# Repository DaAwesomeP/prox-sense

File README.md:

prox-sense
==========

[prox-sense](https://github.com/DaAwesomeP/prox-sense) is a series of printed
circuit board (PCB) designs for designed to bring robust and discreet
capacitive proximity and touch sensing to artists and makers.

**Video demonstration and poster: [Hidden Touch: Open Source Sensors for New
Interaction](https://perrynaseck.com/work/prox-sense/)**

This repository contains the KiCAD schematics, boards, and Gerber files
required to produce the sensing boards. License notice below.

## Premise

**Existing systems for creating interactive experiences:**

 - Expensive
 - Can be difficult to use or understand
 - Limited or nonexistent proximity detection (existing capacitive options)
 - Dense arrangements of proximity sensors may not function (existing
   capacitive options)
 - Connectivity options do not scale up to large systems of sensors
 - Equivalent/alternative optical systems are intrusive, expensive, or
   predictable (cameras, vision systems)
 - Require large amounts of processing or setup
 - Existing tactile systems are predictable (buttons, knobs, touchscreens,
   etc.)

**prox-sense promotes discoverable and new interactions:**

 - Inexpensive
 - Focus on proximity detection
 - Proximity through solid and opaque objects (sensors can be entirely hidden)
 - Directional proximity detection options allow for dense arrangements
 - Interaction is led by the objects the sensors are hidden in and the
   resulting interactions, not the sensors and sensor limitations
 - Small sensors allow for small detection areas and objects
 - Simple connectivity scales up to large systems without limiting the maximum
   number of easily-connected sensors
 - Open source and free to produce

## Boards

Currently all boards are based around the [Microchip
MTCH105](https://www.microchip.com/en-us/product/MTCH105)

 - Simple GPIO interface for detection and sensitivity adjustment. The standard
   logic output can be used directly with microcontrollers, logic circuits,
   transistors, muxes, and port expanders
 - Rejects liquids and other uncertain signal sources
 - Supports guard reference signal for solid interference mitigation
 - All boards currently use the same schematic but vary the copper/trace layout
   to achieve different detection patterns

### Directional board

 - Detects proximity and touch only directly in front of the sensors
 - Rejects rear and off-axis (side) detection using guard signal
 - Guard signal on edge allows for close-packing of sensors

### Omnidirectional board

 - Detects proximity and touch from all directions
 - Guard signal on edge allows for close-packing of sensors

## License Notice
Copyright Perry Naseck 2022.

This source describes Open Hardware and is licensed under the CERN-OHL-S v2.

You may redistribute and modify this source and make products using it under
the terms of the CERN-OHL-S v2 (https://ohwr.org/cern_ohl_s_v2.txt).

This source is distributed WITHOUT ANY EXPRESS OR IMPLIED WARRANTY,
INCLUDING OF MERCHANTABILITY, SATISFACTORY QUALITY AND FITNESS FOR A
PARTICULAR PURPOSE. Please see the CERN-OHL-S v2 for applicable conditions.

Source location: https://github.com/DaAwesomeP/prox-sense

As per CERN-OHL-S v2 section 4, should You produce hardware based on this
source, You must where practicable maintain the Source Location visible
on the external case of the prox-sense or other products you make using this
source.

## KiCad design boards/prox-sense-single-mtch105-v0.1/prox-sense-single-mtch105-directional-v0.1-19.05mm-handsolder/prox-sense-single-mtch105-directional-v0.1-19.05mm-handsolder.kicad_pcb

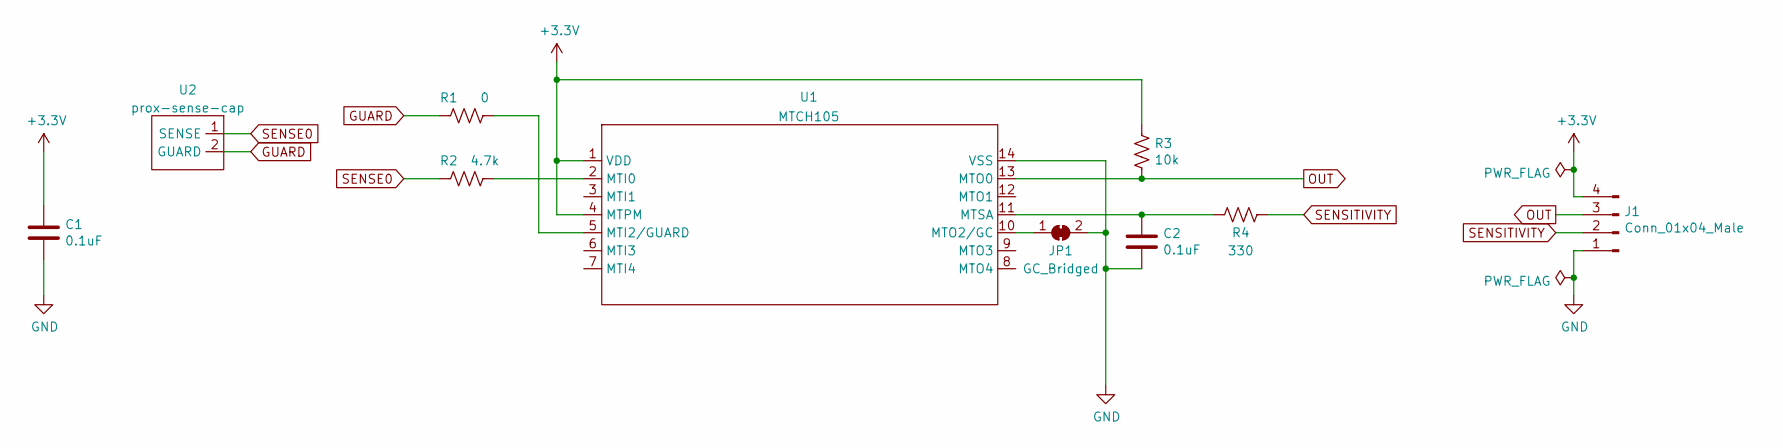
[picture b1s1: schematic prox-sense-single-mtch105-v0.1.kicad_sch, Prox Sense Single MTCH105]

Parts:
C1, C2: 0.1uF; C_0603_1608Metric_Pad1.08x0.95mm_HandSolder
J1: Conn_01x04_Male; PinHeader_1x04_P2.54mm_Vertical
JP1: GC_Bridged; SolderJumper-2_P1.3mm_Bridged_Pad1.0x1.5mm
R1: 0; R_0603_1608Metric_Pad0.98x0.95mm_HandSolder
R2: 4.7k; R_0603_1608Metric_Pad0.98x0.95mm_HandSolder
R3: 10k; R_0603_1608Metric_Pad0.98x0.95mm_HandSolder
R4: 330; R_0603_1608Metric_Pad0.98x0.95mm_HandSolder
U1: MTCH105; MTCH105-I&slash_ST
U2: prox-sense-cap; prox-sense-cap-omni-19.05mm

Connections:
+3V3: C1.1, J1.4, R3.1, U1.1 (VDD), U1.4 (MTPM)
GND: C1.2, C2.2, J1.1, JP1.2 (B), U1.14 (VSS)
GUARD: R1.2, U2.2 (GUARD)
unnamed: C2.1, R4.2, U1.11 (MTSA)
unnamed: JP1.1 (A), U1.10 (MTO2/GC)
unnamed: R1.1, U1.5 (MTI2/GUARD)
unnamed: R2.1, U1.2 (MTI0)
OUT: J1.3, R3.2, U1.13 (MTO0)
SENSE0: R2.2, U2.1 (SENSE)
SENSITIVITY: J1.2, R4.1

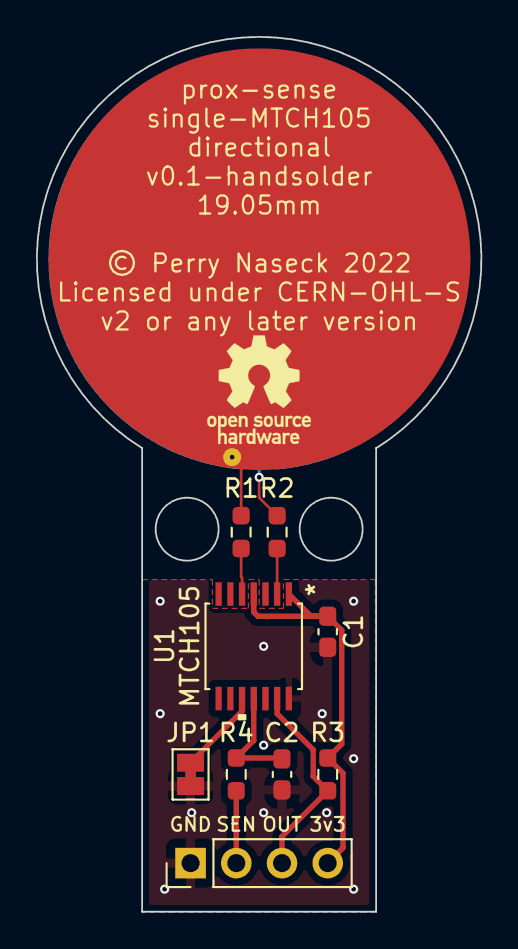
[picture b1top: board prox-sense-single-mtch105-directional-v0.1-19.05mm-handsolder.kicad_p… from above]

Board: 2 copper layers, 24.7 x 48.6 mm, 10 parts (1 on the bottom side), 10 nets.

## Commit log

2022-03-10 initial
2022-03-10 gerber zip, omni guard on one side, no vias
2022-03-10 smaller directional guard via
2022-11-17 new photos, readme text
2022-11-17 fix README image
2022-11-17 fix README image size
2022-11-17 fix README image size (larger)
2022-11-17 fix README bold premise sections
2022-11-17 add link to video and poster
2022-11-17 fix formatting typo

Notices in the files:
boards/prox-sense-single-mtch105-v0.1/prox-sense-single-mtch105-directional-v0.1-19.05mm-handsolder/prox-sense-single-mtch105-directional-v0.1-19.05mm-handsolder.kicad_pcb:
Copyright Perry Naseck 2022; licensed under CERN-OHL-S v2 or any later version
© Perry Naseck 2022
parts and their libraries:
Copyright 2021 Accelerated Designs. All rights reserved.
